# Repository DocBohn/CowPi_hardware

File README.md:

# CowPi_hardware
Hardware designs for Cow Pi educational boards

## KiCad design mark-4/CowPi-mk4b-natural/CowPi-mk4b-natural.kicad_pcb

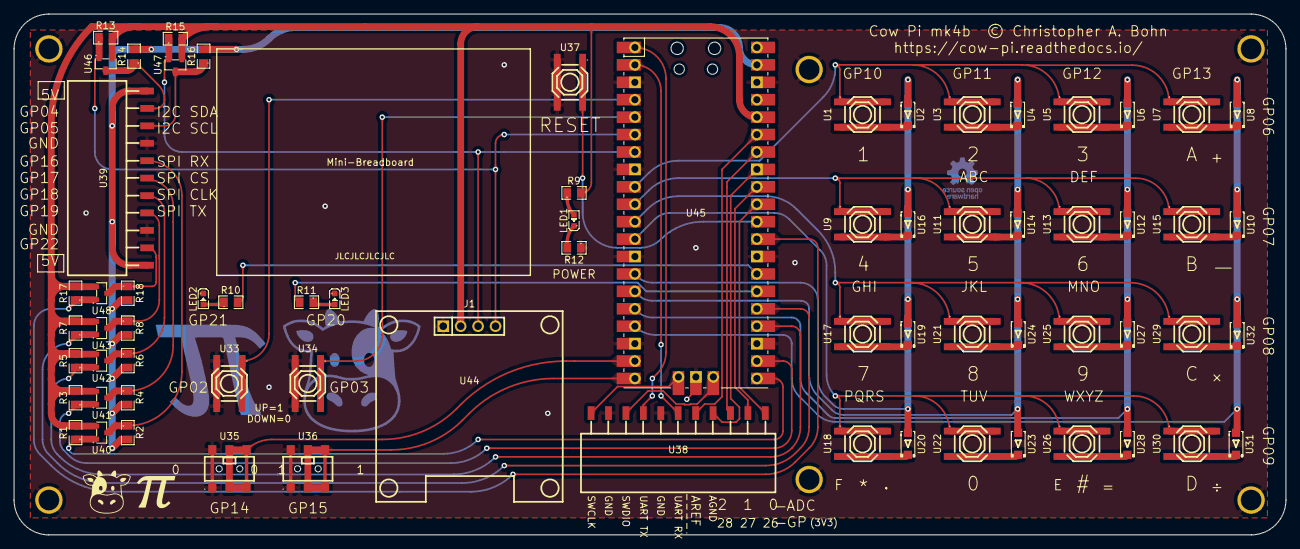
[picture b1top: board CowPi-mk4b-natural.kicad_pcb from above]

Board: 2 copper layers, 185.4 x 75.9 mm, 76 parts (0 on the bottom side), 61 nets.

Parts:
H1, H2, H3, H4, H5, H6: MountingHole; MountingHole_3mm_Pad
J1: PH-00015; HDR-TH_4P-P2.54-V-M
LED1, LED2, LED3: KT-0603R; LED0603-RD
R1, R2, R3, R4, R5, R6, R7, R8, R13, R14, R15, R16, R17, R18: 0805W8F1002T5E; R0805
R9, R10, R11, R12: 0805W8F1001T5E; R0805
U1, U3, U5, U7, U9, U11, U13, U15, U17, U18, U21, U22, U25, U26, U29, U30, U33, U34, U37: TS-1187A-B-A-B; SW-SMD_4P-L5.1-W5.1-P3.70-LS6.5-TL-2
U2, U4, U6, U8, U10, U12, U14, U16, U19, U20, U23, U24, U27, U28, U31, U32: 1N4001_C2892326; SOD-123FL_L2.8-W1.8-LS3.7-RD
U35, U36: SS-3390S-L0; SW-SMD_6P-P2.50_L3.5-W7.2
U38, U39: X6511FRS-11-C85D30; HDR-SMD_11P-P2.54-H-F-L11.5
U40, U41, U42, U43, U46, U47, U48: BSS138_C3015220; SOT-23-3_L2.9-W1.3-P1.90-LS2.4-BR-1
U44: HS96L03W2C03; OLED-TH_L27.8-W27.2-P2.54_C9900033791
U45: Pico; RPi_Pico_SMD_TH

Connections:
/3V3: J1.2, R1.2, R3.2, R5.2, R7.2, R9.2, R13.2, R15.2, R17.2, U40.1 (G), U41.1 (G), U42.1 (G), U43.1 (G), U45.36 (3V3), U46.1 (G), U47.1 (G), U48.1 (G)
/ADC_VREF: U38.7, U45.35 (ADC_VREF)
/AGND: U38.8, U45.33 (AGND)
/Col1: U2.2 (A), U16.2 (A), U19.2 (A), U20.2 (A), U45.14 (GPIO10)
/Col2: U4.2 (A), U14.2 (A), U23.2 (A), U24.2 (A), U45.15 (GPIO11)
/Col3: U6.2 (A), U12.2 (A), U27.2 (A), U28.2 (A), U45.16 (GPIO12)
/ColA: U8.2 (A), U10.2 (A), U31.2 (A), U32.2 (A), U45.17 (GPIO13)
/GND: H1.1, H2.1, H3.1, H4.1, H5.1, H6.1, J1.1, LED2.1 (K), LED3.1 (K), R12.1, U33.3 (C), U33.4 (D), U34.3 (C), U34.4 (D), U35.1, U35.4, U36.1, U36.4, U37.3 (C), U37.4 (D), U38.2, U38.5, U39.4, U39.9, U45.3 (GND), U45.8 (GND), U45.13 (GND), U45.18 (GND), U45.23 (GND), U45.28 (GND), U45.38 (GND), U45.42 (GND)
/GP26_ADC0: U38.11, U45.31 (GPIO26_ADC0)
/GP27_ADC1: U38.10, U45.32 (GPIO27_ADC1)
/GP28_ADC2: U38.9, U45.34 (GPIO28_ADC2)
/HV_GP04_I2C_SDA: R14.1, U39.2, U46.3 (D)
/HV_GP05_I2C_SCL: R16.1, U39.3, U47.3 (D)
/HV_GP16_SPI_RX: R2.1, U39.5, U40.3 (D)
/HV_GP17_SPI_CS: R4.1, U39.6, U41.3 (D)
/HV_GP18_SPI_CLK: R6.1, U39.7, U42.3 (D)
/HV_GP19_SPI_TX: R8.1, U39.8, U43.3 (D)
/HV_GP22: R18.1, U39.10, U48.3 (D)
/LV_GP04_I2C_SDA: J1.4, R13.1, U45.6 (GPIO4), U46.2 (S)
/LV_GP05_I2C_SCL: J1.3, R15.1, U45.7 (GPIO5), U47.2 (S)
/LV_GP16_SPI_RX: R1.1, U40.2 (S), U45.21 (GPIO16)
/LV_GP17_SPI_CS: R3.1, U41.2 (S), U45.22 (GPIO17)
/LV_GP18_SPI_CLK: R5.1, U42.2 (S), U45.24 (GPIO18)
/LV_GP19_SPI_TX: R7.1, U43.2 (S), U45.25 (GPIO19)
/LV_GP22: R17.1, U45.29 (GPIO22), U48.2 (S)
/LeftButton: U33.1 (A), U33.2 (B), U45.4 (GPIO2)
/LeftLED: R10.2, U45.27 (GPIO21)
/LeftSwitch: U35.2, U35.3, U35.5, U35.6, U45.19 (GPIO14)
/RUN: U37.1 (A), U37.2 (B), U45.30 (RUN)
/RightButton: U34.1 (A), U34.2 (B), U45.5 (GPIO3)
/RightLED: R11.2, U45.26 (GPIO20)
/RightSwitch: U36.2, U36.3, U36.5, U36.6, U45.20 (GPIO15)
/Row1: U1.1 (A), U1.2 (B), U3.1 (A), U3.2 (B), U5.1 (A), U5.2 (B), U7.1 (A), U7.2 (B), U45.9 (GPIO6)
/Row4: U9.1 (A), U9.2 (B), U11.1 (A), U11.2 (B), U13.1 (A), U13.2 (B), U15.1 (A), U15.2 (B), U45.10 (GPIO7)
/Row7: U17.1 (A), U17.2 (B), U21.1 (A), U21.2 (B), U25.1 (A), U25.2 (B), U29.1 (A), U29.2 (B), U45.11 (GPIO8)
/Row*: U18.1 (A), U18.2 (B), U22.1 (A), U22.2 (B), U26.1 (A), U26.2 (B), U30.1 (A), U30.2 (B), U45.12 (GPIO9)
/SWCLK: U38.1, U45.41 (SWCLK)
/SWDIO: U38.3, U45.43 (SWDIO)
/UART_RX: U38.6, U45.2 (GPIO1)
/UART_TX: U38.4, U45.1 (GPIO0)
/VSYS: R2.2, R4.2, R6.2, R8.2, R14.2, R16.2, R18.2, U39.1, U39.11, U45.39 (VSYS)
unnamed: LED1.2 (A), R9.1
unnamed: LED1.1 (K), R12.2
unnamed: LED2.2 (A), R10.1
unnamed: LED3.2 (A), R11.1
unnamed: U1.3 (C), U1.4 (D), U2.1 (K)
unnamed: U3.3 (C), U3.4 (D), U4.1 (K)
unnamed: U5.3 (C), U5.4 (D), U6.1 (K)
unnamed: U7.3 (C), U7.4 (D), U8.1 (K)
unnamed: U10.1 (K), U15.3 (C), U15.4 (D)
unnamed: U11.3 (C), U11.4 (D), U14.1 (K)
unnamed: U12.1 (K), U13.3 (C), U13.4 (D)
unnamed: U9.3 (C), U9.4 (D), U16.1 (K)
unnamed: U17.3 (C), U17.4 (D), U19.1 (K)
unnamed: U18.3 (C), U18.4 (D), U20.1 (K)
unnamed: U21.3 (C), U21.4 (D), U24.1 (K)
unnamed: U22.3 (C), U22.4 (D), U23.1 (K)
unnamed: U25.3 (C), U25.4 (D), U27.1 (K)
unnamed: U26.3 (C), U26.4 (D), U28.1 (K)
unnamed: U29.3 (C), U29.4 (D), U32.1 (K)
unnamed: U30.3 (C), U30.4 (D), U31.1 (K)

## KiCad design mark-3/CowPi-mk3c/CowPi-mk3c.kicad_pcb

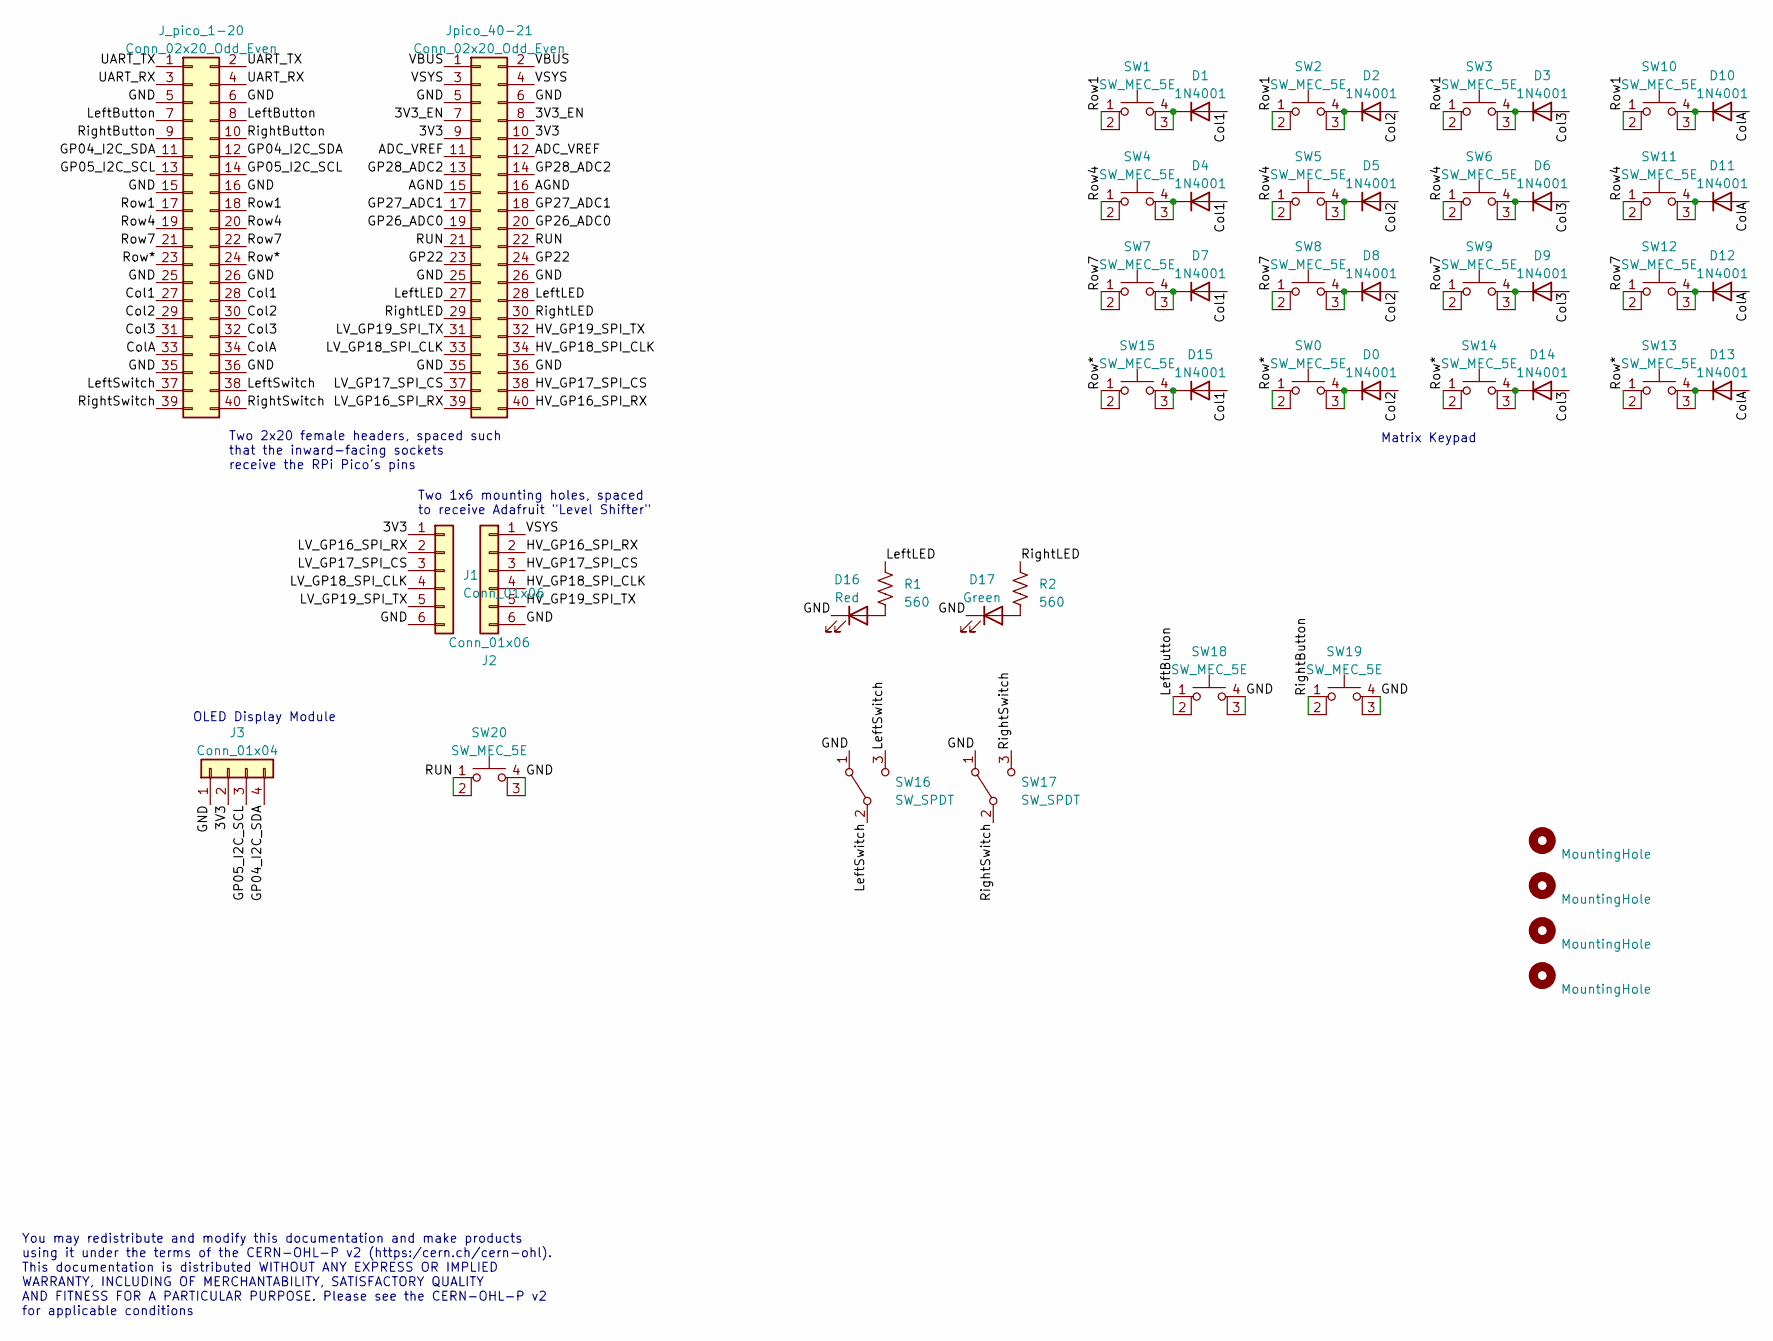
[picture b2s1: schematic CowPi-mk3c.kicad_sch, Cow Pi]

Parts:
D0, D1, D2, D3, D4, D5, D6, D7, D8, D9, D10, D11, D12, D13, D14, D15: 1N4001; D_DO-41_SOD81_P3.81mm_Vertical_AnodeUp
D16: Red; LED_D5.0mm
D17: Green; LED_D5.0mm
H1, H2, H3, H4: MountingHole; MountingHole_3mm_Pad
J1, J2: Conn_01x06; PinSocket_1x06_P2.54mm_Vertical
J3: Conn_01x04; PinSocket_1x04_P2.54mm_Vertical
J_pico_1-20: Conn_02x20_Odd_Even; PinHeader_2x20_P2.54mm_Vertical
Jpico_40-21: Conn_02x20_Odd_Even; PinHeader_2x20_P2.54mm_Vertical
R1, R2: 560; R_Axial_DIN0309_L9.0mm_D3.2mm_P2.54mm_Vertical
SW0, SW1, SW2, SW3, SW4, SW5, SW6, SW7, SW8, SW9, SW10, SW11, SW12, SW13, SW14, SW15, SW18, SW19, SW20: SW_MEC_5E; SW_PUSH_6mm
SW16, SW17: SW_SPDT; SW_Slide_1P2T_CK_OS102011MS2Q

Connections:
/3V3: J1.1, J3.2, Jpico_40-21.9, Jpico_40-21.10
/3V3_EN: Jpico_40-21.7, Jpico_40-21.8
/ADC_VREF: Jpico_40-21.11, Jpico_40-21.12
/AGND: Jpico_40-21.15, Jpico_40-21.16
/Col1: D1.2 (A), D4.2 (A), D7.2 (A), D15.2 (A), J_pico_1-20.27, J_pico_1-20.28
/Col2: D0.2 (A), D2.2 (A), D5.2 (A), D8.2 (A), J_pico_1-20.29, J_pico_1-20.30
/Col3: D3.2 (A), D6.2 (A), D9.2 (A), D14.2 (A), J_pico_1-20.31, J_pico_1-20.32
/ColA: D10.2 (A), D11.2 (A), D12.2 (A), D13.2 (A), J_pico_1-20.33, J_pico_1-20.34
/GND: D16.1 (K), D17.1 (K), J1.6, J2.6, J3.1, J_pico_1-20.5, J_pico_1-20.6, J_pico_1-20.15, J_pico_1-20.16, J_pico_1-20.25, J_pico_1-20.26, J_pico_1-20.35, J_pico_1-20.36, Jpico_40-21.5, Jpico_40-21.6, Jpico_40-21.25, Jpico_40-21.26, Jpico_40-21.35, Jpico_40-21.36, SW16.1 (A), SW17.1 (A), SW18.3 (K), SW18.4 (A), SW19.3 (K), SW19.4 (A), SW20.3 (K), SW20.4 (A)
/GP04_I2C_SDA: J3.4, J_pico_1-20.11, J_pico_1-20.12
/GP05_I2C_SCL: J3.3, J_pico_1-20.13, J_pico_1-20.14
/GP22: Jpico_40-21.23, Jpico_40-21.24
/GP26_ADC0: Jpico_40-21.19, Jpico_40-21.20
/GP27_ADC1: Jpico_40-21.17, Jpico_40-21.18
/GP28_ADC2: Jpico_40-21.13, Jpico_40-21.14
/HV_GP16_SPI_RX: J2.2, Jpico_40-21.40
/HV_GP17_SPI_CS: J2.3, Jpico_40-21.38
/HV_GP18_SPI_CLK: J2.4, Jpico_40-21.34
/HV_GP19_SPI_TX: J2.5, Jpico_40-21.32
/LV_GP16_SPI_RX: J1.2, Jpico_40-21.39
/LV_GP17_SPI_CS: J1.3, Jpico_40-21.37
/LV_GP18_SPI_CLK: J1.4, Jpico_40-21.33
/LV_GP19_SPI_TX: J1.5, Jpico_40-21.31
/LeftButton: J_pico_1-20.7, J_pico_1-20.8, SW18.1, SW18.2
/LeftLED: Jpico_40-21.27, Jpico_40-21.28, R1.1
/LeftSwitch: J_pico_1-20.37, J_pico_1-20.38, SW16.2 (B), SW16.3 (C)
/RUN: Jpico_40-21.21, Jpico_40-21.22, SW20.1, SW20.2
/RightButton: J_pico_1-20.9, J_pico_1-20.10, SW19.1, SW19.2
/RightLED: Jpico_40-21.29, Jpico_40-21.30, R2.1
/RightSwitch: J_pico_1-20.39, J_pico_1-20.40, SW17.2 (B), SW17.3 (C)
/Row1: J_pico_1-20.17, J_pico_1-20.18, SW1.1, SW1.2, SW2.1, SW2.2, SW3.1, SW3.2, SW10.1, SW10.2
/Row4: J_pico_1-20.19, J_pico_1-20.20, SW4.1, SW4.2, SW5.1, SW5.2, SW6.1, SW6.2, SW11.1, SW11.2
/Row7: J_pico_1-20.21, J_pico_1-20.22, SW7.1, SW7.2, SW8.1, SW8.2, SW9.1, SW9.2, SW12.1, SW12.2
/Row*: J_pico_1-20.23, J_pico_1-20.24, SW0.1, SW0.2, SW13.1, SW13.2, SW14.1, SW14.2, SW15.1, SW15.2
/UART_RX: J_pico_1-20.3, J_pico_1-20.4
/UART_TX: J_pico_1-20.1, J_pico_1-20.2
/VBUS: Jpico_40-21.1, Jpico_40-21.2
/VSYS: J2.1, Jpico_40-21.3, Jpico_40-21.4
unnamed: D0.1 (K), SW0.3 (K), SW0.4 (A)
unnamed: D1.1 (K), SW1.3 (K), SW1.4 (A)
unnamed: D2.1 (K), SW2.3 (K), SW2.4 (A)
unnamed: D3.1 (K), SW3.3 (K), SW3.4 (A)
unnamed: D4.1 (K), SW4.3 (K), SW4.4 (A)
unnamed: D5.1 (K), SW5.3 (K), SW5.4 (A)
unnamed: D6.1 (K), SW6.3 (K), SW6.4 (A)
unnamed: D7.1 (K), SW7.3 (K), SW7.4 (A)
unnamed: D8.1 (K), SW8.3 (K), SW8.4 (A)
unnamed: D9.1 (K), SW9.3 (K), SW9.4 (A)
unnamed: D10.1 (K), SW10.3 (K), SW10.4 (A)
unnamed: D11.1 (K), SW11.3 (K), SW11.4 (A)
unnamed: D12.1 (K), SW12.3 (K), SW12.4 (A)
unnamed: D13.1 (K), SW13.3 (K), SW13.4 (A)
unnamed: D14.1 (K), SW14.3 (K), SW14.4 (A)
unnamed: D15.1 (K), SW15.3 (K), SW15.4 (A)
unnamed: D16.2 (A), R1.2
unnamed: D17.2 (A), R2.2

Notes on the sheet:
OLED Display Module
Two 1x6 mounting holes, spaced to receive Adafruit "Level Shifter"
Matrix Keypad
You may redistribute and modify this documentation and make products using it under the terms of the CERN-OHL-P v2 (https:/cern.ch/cern-ohl). This documentation is distributed WITHOUT ANY EXPRESS OR IMPLIED WARRANTY, INCLUDING OF MERCHANTABILITY, SATISFACTORY QUALITY AND FITNESS FOR A PARTICULAR PU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
Two 2x20 female headers, spaced such that the inward-facing sockets receive the RPi Pico's pins

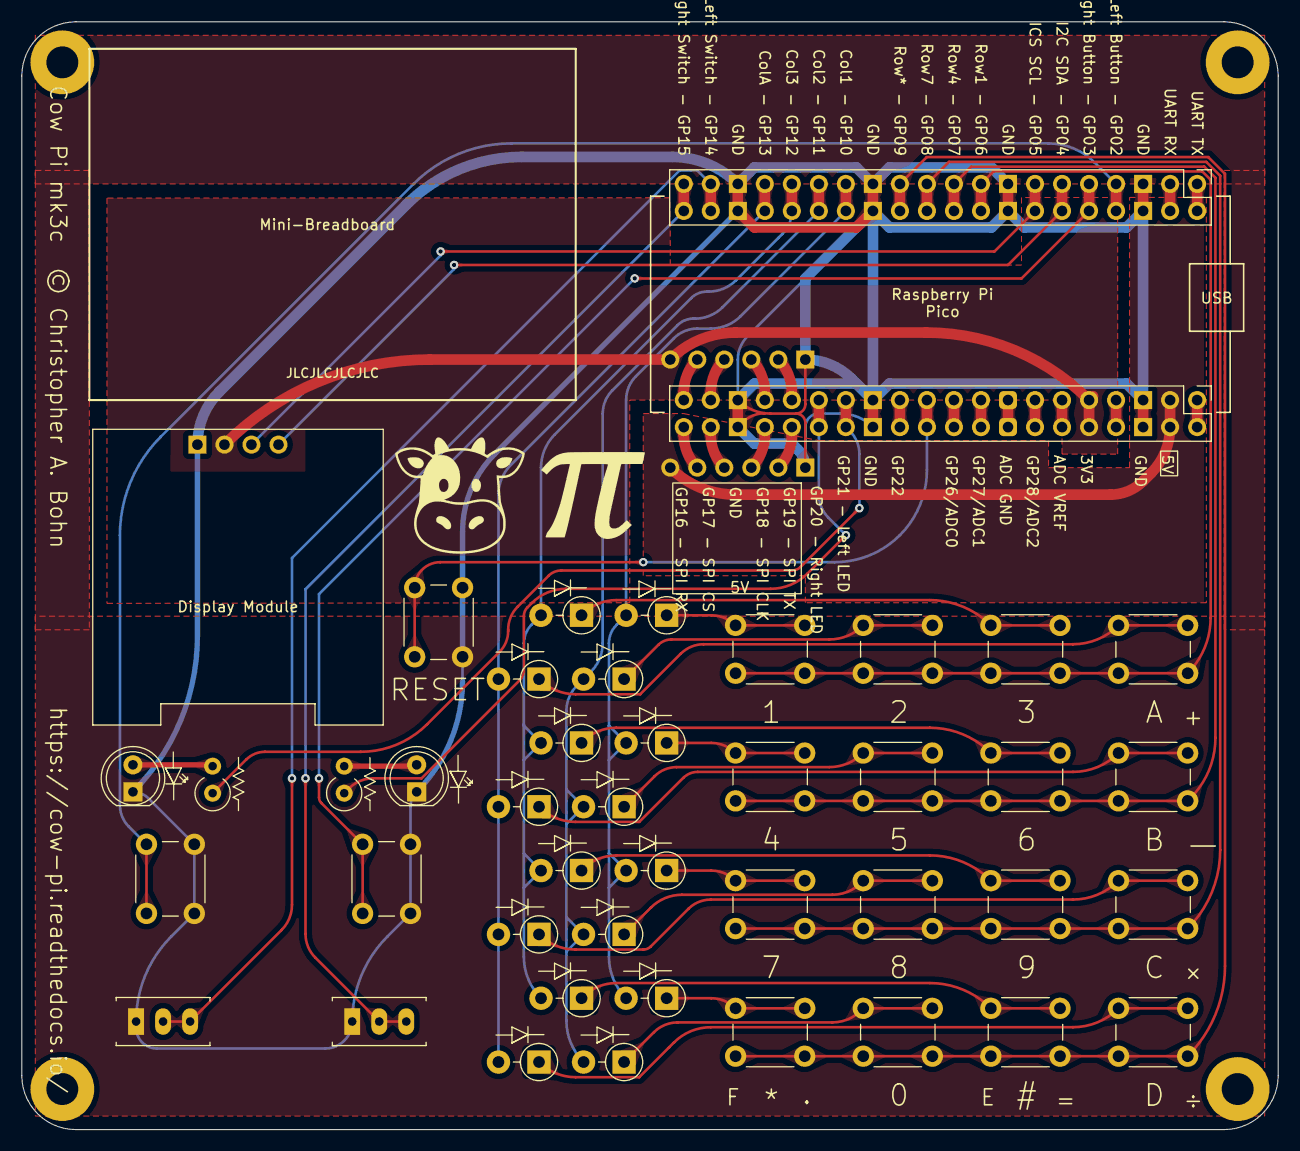
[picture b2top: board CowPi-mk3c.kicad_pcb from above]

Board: 2 copper layers, 118.1 x 104.1 mm, 50 parts (0 on the bottom side), 56 nets.

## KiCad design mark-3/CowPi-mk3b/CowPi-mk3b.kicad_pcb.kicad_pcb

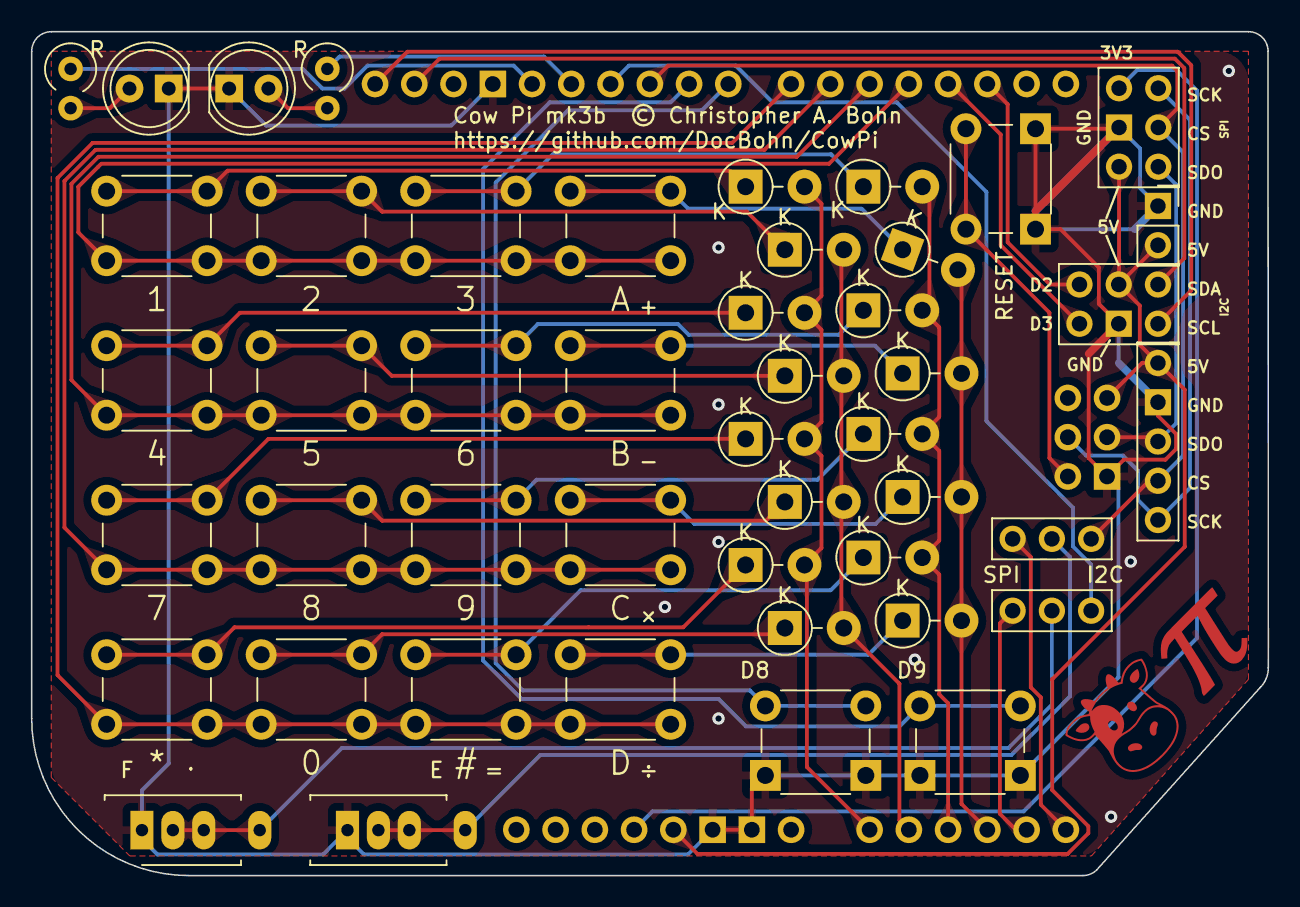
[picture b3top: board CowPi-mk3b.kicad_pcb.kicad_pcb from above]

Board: 2 copper layers, 80.0 x 54.6 mm, 47 parts (0 on the bottom side), 45 nets.

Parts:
0: Key 0; SW_PUSH_6mm_H5mm
1: Key 1; SW_PUSH_6mm_H5mm
2: Key 2; SW_PUSH_6mm_H5mm
3: Key 3; SW_PUSH_6mm_H5mm
4: Key 4; SW_PUSH_6mm_H5mm
5: Key 5; SW_PUSH_6mm_H5mm
6: Key 6; SW_PUSH_6mm_H5mm
7: Key 7; SW_PUSH_6mm_H5mm
8: Key 8; SW_PUSH_6mm_H5mm
9: Key 9; SW_PUSH_6mm_H5mm
*: Key *; SW_PUSH_6mm_H5mm
A: Key A; SW_PUSH_6mm_H5mm
B: Key B; SW_PUSH_6mm_H5mm
C: Key C; SW_PUSH_6mm_H5mm
D: Key D; SW_PUSH_6mm_H5mm
D1, D2, D3, D4, D5, D6, D7, D8, D9, D10, D11, D12, D13, D14, D15, D16: 1N4001; D_DO-41_SOD81_P3.81mm_Vertical_AnodeUp
D17: Red; LED_D5.0mm
D18: Green; LED_D5.0mm
J1, J2: Conn_02x03_Counter_Clockwise; PinSocket_2x03_P2.54mm_Vertical
J3: Conn_01x02; PinSocket_1x02_P2.54mm_Vertical
J4: Conn_01x05; PinSocket_1x05_P2.54mm_Vertical
JP1, JP2: Jumper_3_Bridged12; PinHeader_1x03_P2.54mm_Vertical
R: 470; R_Axial_DIN0309_L9.0mm_D3.2mm_P2.54mm_Vertical
R#2: 470; R_Axial_DIN0309_L9.0mm_D3.2mm_P2.54mm_Vertical
RESET: RESET; SW_PUSH_6mm_H5mm
SW17: Left Button; SW_PUSH_6mm_H5mm
SW18: Right Button; SW_PUSH_6mm_H5mm
SW20: Left Switch; SW_Slide_1P2T_CK_OS102011MS2Q
SW21: Right Switch; SW_Slide_1P2T_CK_OS102011MS2Q
XA1: Arduino_Uno_R3_Shield

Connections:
/3V3: J1.2, XA1.3V3 (3.3V)
/5V: J1.6, J2.3, J3.2, J4.1, XA1.5V1 (5V), XA1.5V2 (SPI_5V)
/CS/i2cRightSwitch: J1.3, J4.4, JP2.3 (B), XA1.D10 (D10_CS)
/D2: J2.1, XA1.D2 (D2_INT0)
/D3: J2.2, XA1.D3 (D3_INT1)
/LeftLED: R.1, XA1.D13
/SCK: J1.1, J4.5, XA1.SCK (SPI_SCK)
/SCL: J2.6, XA1.SCL
/SDA: J2.5, XA1.SDA
/SDO: J1.5, J4.3, XA1.MOSI (SPI_MOSI)
/col1: D1.2 (A), D2.2 (A), D3.2 (A), D4.2 (A), XA1.A0
/col2: D5.2 (A), D6.2 (A), D7.2 (A), D8.2 (A), XA1.A1
/col3: D9.2 (A), D10.2 (A), D11.2 (A), D12.2 (A), XA1.A2
/colA: D13.2 (A), D14.2 (A), D15.2 (A), D16.2 (A), XA1.A3
/i2cLeftSwitch: JP1.3 (B), XA1.D11
/leftButton: SW17.3 (K), SW17.4 (A), XA1.D8
/rightButton: SW18.1, SW18.2, XA1.D9
/rightLED: R#2.1, XA1.D12
/row1: 1.1, 1.2, 2.1, 2.2, 3.1, 3.2, A.1, A.2, XA1.D4
/row4: 4.1, 4.2, 5.1, 5.2, 6.1, 6.2, B.1, B.2, XA1.D5
/row7: 7.1, 7.2, 8.1, 8.2, 9.1, 9.2, C.1, C.2, XA1.D6
/row*: 0.1, 0.2, *.1, *.2, D.1, D.2, XA1.D7
/spiLeftSwitch: JP1.1 (A), XA1.A4
/spiRightSwitch: JP2.1 (A), XA1.A5
GND: D17.1 (K), D18.1 (K), J1.4, J2.4, J3.1, J4.2, RESET.1, RESET.2, SW17.1, SW17.2, SW18.3 (K), SW18.4 (A), SW20.1 (A), SW21.1 (A), XA1.GND1 (GND), XA1.GND2 (GND), XA1.GND3 (GND), XA1.GND4 (SPI_GND)
unnamed: 1.3 (2), 1.4 (2), D1.1 (K)
unnamed: 4.3 (2), 4.4 (2), D2.1 (K)
unnamed: 7.3 (2), 7.4 (2), D3.1 (K)
unnamed: *.3 (2), *.4 (2), D4.1 (K)
unnamed: 2.3 (2), 2.4 (2), D5.1 (K)
unnamed: 5.3 (2), 5.4 (2), D6.1 (K)
unnamed: 8.3 (2), 8.4 (2), D7.1 (K)
unnamed: 0.3 (2), 0.4 (2), D8.1 (K)
unnamed: 3.3 (2), 3.4 (2), D9.1 (K)
unnamed: 6.3 (2), 6.4 (2), D10.1 (K)
unnamed: 9.3 (2), 9.4 (2), D11.1 (K)
unnamed: A.3 (2), A.4 (2), D13.1 (K)
unnamed: B.3 (2), B.4 (2), D14.1 (K)
unnamed: C.3 (2), C.4 (2), D15.1 (K)
unnamed: D.3 (2), D.4 (2), D16.1 (K)
unnamed: D17.2 (A), R.2
unnamed: D18.2 (A), R#2.2
unnamed: JP1.2 (C), SW20.2 (B)
unnamed: JP2.2 (C), SW21.2 (B)
unnamed: RESET.3 (2), RESET.4 (2), XA1.RST2 (SPI_RESET)

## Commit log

2023-07-17 Add license
2023-07-17 Added on-hand design files
    Fritzing files for each Mark 1 version
    Layout notes for Mark 2b
    KiCad files for each Mark 3 version
2023-07-30 added Cow Pi mk3c
2023-09-07 Corrected silkscreen for mk3c
2023-09-16 CowPi mk4a ready for LRIP
2023-10-03 Mark 4b just about ready for LRIP
2023-10-19 created version of mk3b that has through-holes for display module
2023-11-30 adding CowPi mk4b BOM file & position file for open sourcing
2023-12-08 updated mk4b gerber with button/switch logic level hints
2025-01-13 Updated mk4b-natural with OSHW certification mark and with alternate slide-switches

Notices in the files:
mark-3/CowPi-mk3b/CowPi-mk3b.kicad_pcb.kicad_pcb:
Cow Pi mk3b  © Christopher A. Bohn
mark-3/CowPi-mk3c/CowPi-mk3c.kicad_pcb:
This source describes Open Hardware and is licensed under the CERN-OHLP v2.
Copyright (c) 2023 Christopher A. Bohn
Licensed under CERN-OHLP v2
Licensed under Apache 2.0
Licensed under CC BY 4.0
Cow Pi mk3c  © Christopher A. Bohn https://cow-pi.readthedocs.io
mark-4/CowPi-mk4b-natural/CowPi-mk4b-natural.kicad_pcb:
This source describes Open Hardware and is licensed under the CRN-OHLP v2.
Cow Pi mk4b  © Christopher A. Bohn
